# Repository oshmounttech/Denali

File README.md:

# Denali
## Overview
The Denali Project is a modular keyboard which can be either a standard 60% keyboard or tricked out to be a full sized keyboard, or a split keyboard, etc. let your mind run wild.

## Build
### Hardware

### Electronics

### Firmware

## How to contribute
Look in the Projects Tab and see what needs to be started/worked on. Remember to document everything so that we can keep the project open and easily buildable.

## A Special Thanks To
- Zack Freedman's MiRage Project
- Stephen Hawes
- KiCAD
- FreeCAD
- GitHub

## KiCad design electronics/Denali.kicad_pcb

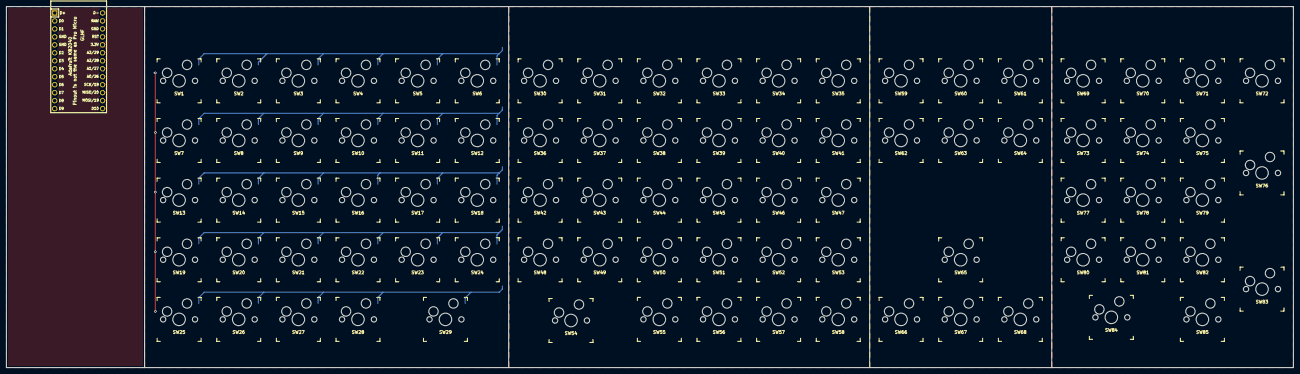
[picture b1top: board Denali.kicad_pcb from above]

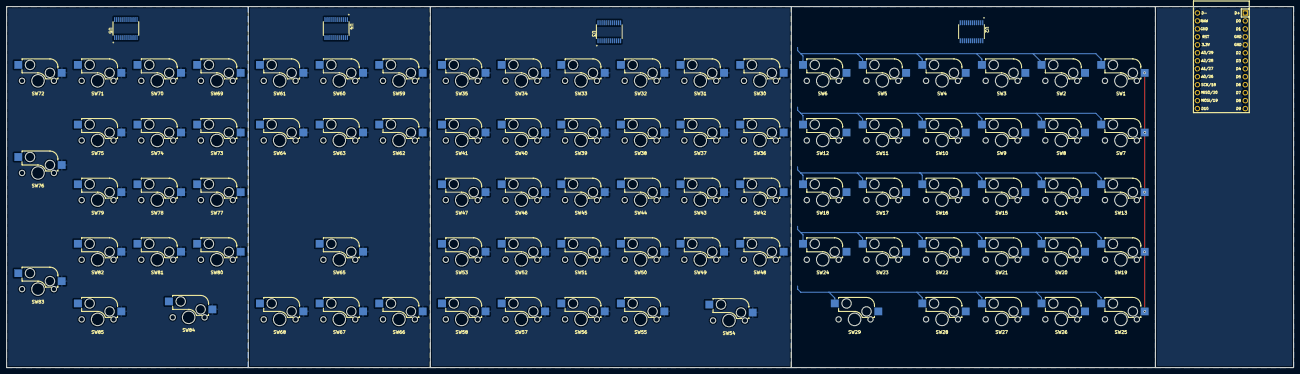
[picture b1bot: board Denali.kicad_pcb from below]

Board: 2 copper layers, 410.0 x 115.0 mm, 90 parts (4 on the bottom side), 16 nets.

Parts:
SW1, SW2, SW3, SW4, SW5, SW6, SW7, SW8, SW9, SW10, SW11, SW12, SW13, SW14, SW15, SW16, SW17, SW18, SW19, SW20, SW21, SW22, SW23, SW24, SW25, SW26, SW27, SW28, SW29, SW30, SW31, SW32, SW33, SW34, SW35, SW36, SW37, SW38, SW39, SW40, SW41, SW42, SW43, SW44, SW45, SW46, SW47, SW48, SW49, SW50, SW51, SW52, SW53, SW54, SW55, SW56, SW57, SW58, SW59, SW60, SW61, SW62, SW63, SW64, SW65, SW66, SW67, SW68, SW69, SW70, SW71, SW72, SW73, SW74, SW75, SW76, SW77, SW78, SW79, SW80, SW81, SW82, SW83, SW84, SW85: SW_SPST; Kailh_socket_MX
U1: kb2040
U2, U3, U4, U5: PCA9675PW; SOP65P640X110-24N

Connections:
COL00: SW1.2 (B), SW7.2 (B), SW13.2 (B), SW19.2 (B), SW25.2 (B)
COL01: SW2.2 (B), SW8.2 (B), SW14.2 (B), SW20.2 (B), SW26.2 (B)
COL02: SW3.2 (B), SW9.2 (B), SW15.2 (B), SW21.2 (B), SW27.2 (B)
COL03: SW4.2 (B), SW10.2 (B), SW16.2 (B), SW22.2 (B), SW28.2 (B)
COL04: SW5.2 (B), SW11.2 (B), SW17.2 (B), SW23.2 (B)
COL05: SW6.2 (B), SW12.2 (B), SW18.2 (B), SW24.2 (B), SW29.2 (B)
GND: SW30.2 (B), SW31.2 (B), SW32.2 (B), SW33.2 (B), SW34.2 (B), SW35.2 (B), SW36.2 (B), SW37.2 (B), SW38.2 (B), SW39.2 (B), SW40.2 (B), SW41.2 (B), SW42.2 (B), SW43.2 (B), SW44.2 (B), SW45.2 (B), SW46.2 (B), SW47.2 (B), SW48.2 (B), SW49.2 (B), SW50.2 (B), SW51.2 (B), SW52.2 (B), SW53.2 (B), SW54.2 (B), SW55.2 (B), SW56.2 (B), SW57.2 (B), SW58.2 (B), SW59.2 (B), SW60.2 (B), SW61.2 (B), SW62.2 (B), SW63.2 (B), SW64.2 (B), SW65.2 (B), SW66.2 (B), SW67.2 (B), SW68.2 (B), SW69.2 (B), SW70.2 (B), SW71.2 (B), SW72.2 (B), SW73.2 (B), SW74.2 (B), SW75.2 (B), SW76.2 (B), SW77.2 (B), SW78.2 (B), SW79.2 (B), SW80.2 (B), SW81.2 (B), SW82.2 (B), SW83.2 (B), SW84.2 (B), SW85.2 (B), U1.4 (GND), U1.5 (GND), U1.16 (GND)
ROW00: SW1.1 (A), SW2.1 (A), SW3.1 (A), SW4.1 (A), SW5.1 (A), SW6.1 (A)
ROW01: SW7.1 (A), SW8.1 (A), SW9.1 (A), SW10.1 (A), SW11.1 (A), SW12.1 (A)
ROW02: SW13.1 (A), SW14.1 (A), SW15.1 (A), SW16.1 (A), SW17.1 (A), SW18.1 (A)
ROW03: SW19.1 (A), SW20.1 (A), SW21.1 (A), SW22.1 (A), SW23.1 (A), SW24.1 (A)
ROW04: SW25.1 (A), SW26.1 (A), SW27.1 (A), SW28.1 (A), SW29.1 (A)
SCL0: U1.13 (D9), U2.22 (SCL), U3.22 (SCL)
SCL1: U1.11 (D7), U4.23 (SDA), U5.23 (SDA)
SDA0: U1.12 (D8), U2.23 (SDA), U3.23 (SDA)
SDA1: U1.10 (D6), U4.22 (SCL), U5.22 (SCL)

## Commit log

2022-06-15 create KiCAD project
2022-06-15 create FreeCAD project
2022-06-15 create python firmware project
2022-06-15 begin documentation
2022-06-15 add left keyboard sheet
2022-06-15 add right keyboard sheet
2022-06-15 add arrow keys and macro pad sheet
2022-06-15 add number pad sheet
2022-06-15 bring all sheets together
2022-06-16 add io expander and switches to schem
2022-06-16 add kb2040 to schem and add io exp and switch
2022-06-16 update project libraries to use links
2022-06-17 update datasheet paths to use links
2022-06-17 change paths to use links
2022-06-17 add freecad logo for documentation
2022-06-17 update KiCAD backups
2022-06-17 update KiCAD backup
2022-06-22 Add Adafruit Library
2022-06-26 ground left keeb switches
2022-06-26 add i2c headers to schematic
2022-06-26 label switch nets
2022-06-26 add components to PCB
2022-06-27 move some switches
2022-06-27 layout components
2022-06-27 fix numberpad switches
2022-06-27 add PCB edge cuts
2022-07-03 update libraries
2022-07-03 change IO expander
2022-07-03 new IO expanders and i2c ideals
2022-07-03 change IO expanders and add 3D models
2022-07-04 begin working on mini-matrix routing
2022-07-04 begin mini-matrix routing
2022-07-11 begin matrix via diodes
2022-07-13 place diodes on left keyboard
2022-07-14 reverse matrix diodes
2022-07-14 work on matrix
2022-07-16 fix right keyboard matrix
2022-07-16 continue work on matrix
2022-07-18 fix matrix on right keyboard
2022-07-18 update KiCAD schematic
2022-07-18 fix num pad matrix
2022-07-18 fix arrow matrix
2022-07-18 work on matrix layout
2022-07-18 fix numpad matrix
2022-07-18 work on PCB matrix
2022-07-19 finish PCB matrix
2022-07-19 import matrix connections
2022-07-19 connect matrix to io expander
2022-07-19 finish left keyboard matrix
2022-07-19 finish matrix
2022-07-19 add mounting holes to pcb
2022-07-19 fix edge cuts
2022-07-19 update diode libraries
2022-07-19 fix silkscreen and edge cuts
2022-07-20 add power and i2c addressing
2022-07-20 add i2c addresses
2022-07-20 add KB2040 firmware
2022-07-21 add i2c tests
2022-07-21 update i2c test
